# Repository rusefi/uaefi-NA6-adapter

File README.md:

# uaefi-NA6-adapter

🔴Community support ONLY 🔴

🟢 https://www.shop.rusefi.com/shop/p/uaefi-adapter-for-na6-definitely-has-issues-please-know-what-you-are-doing 🟢

To be used with https://github.com/rusefi/uaefi

powered by [rusEFI firmware](https://github.com/rusefi/rusefi)

## fun fact

See https://wiki.rusefi.com/Miata/#mazda-miata for (legacy?) open source Plug and plays

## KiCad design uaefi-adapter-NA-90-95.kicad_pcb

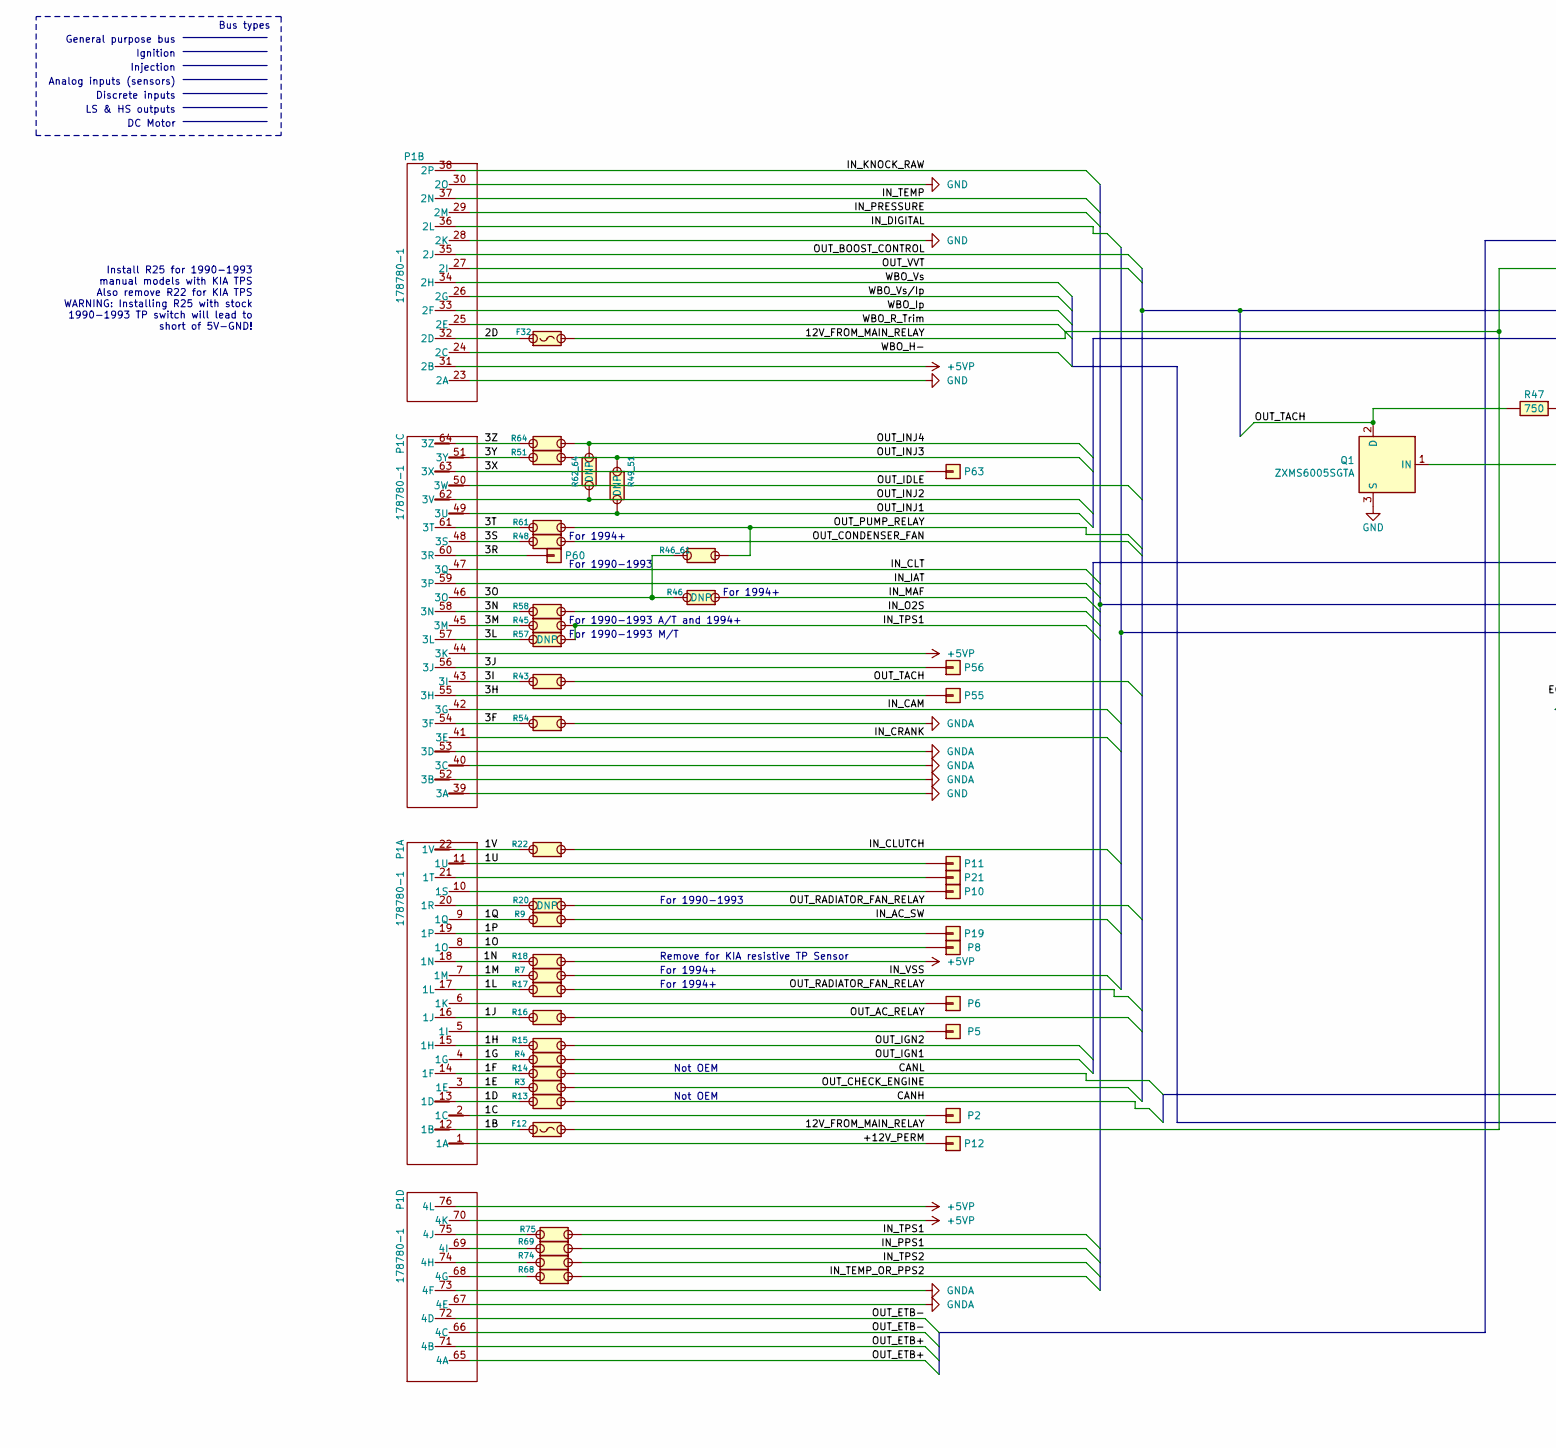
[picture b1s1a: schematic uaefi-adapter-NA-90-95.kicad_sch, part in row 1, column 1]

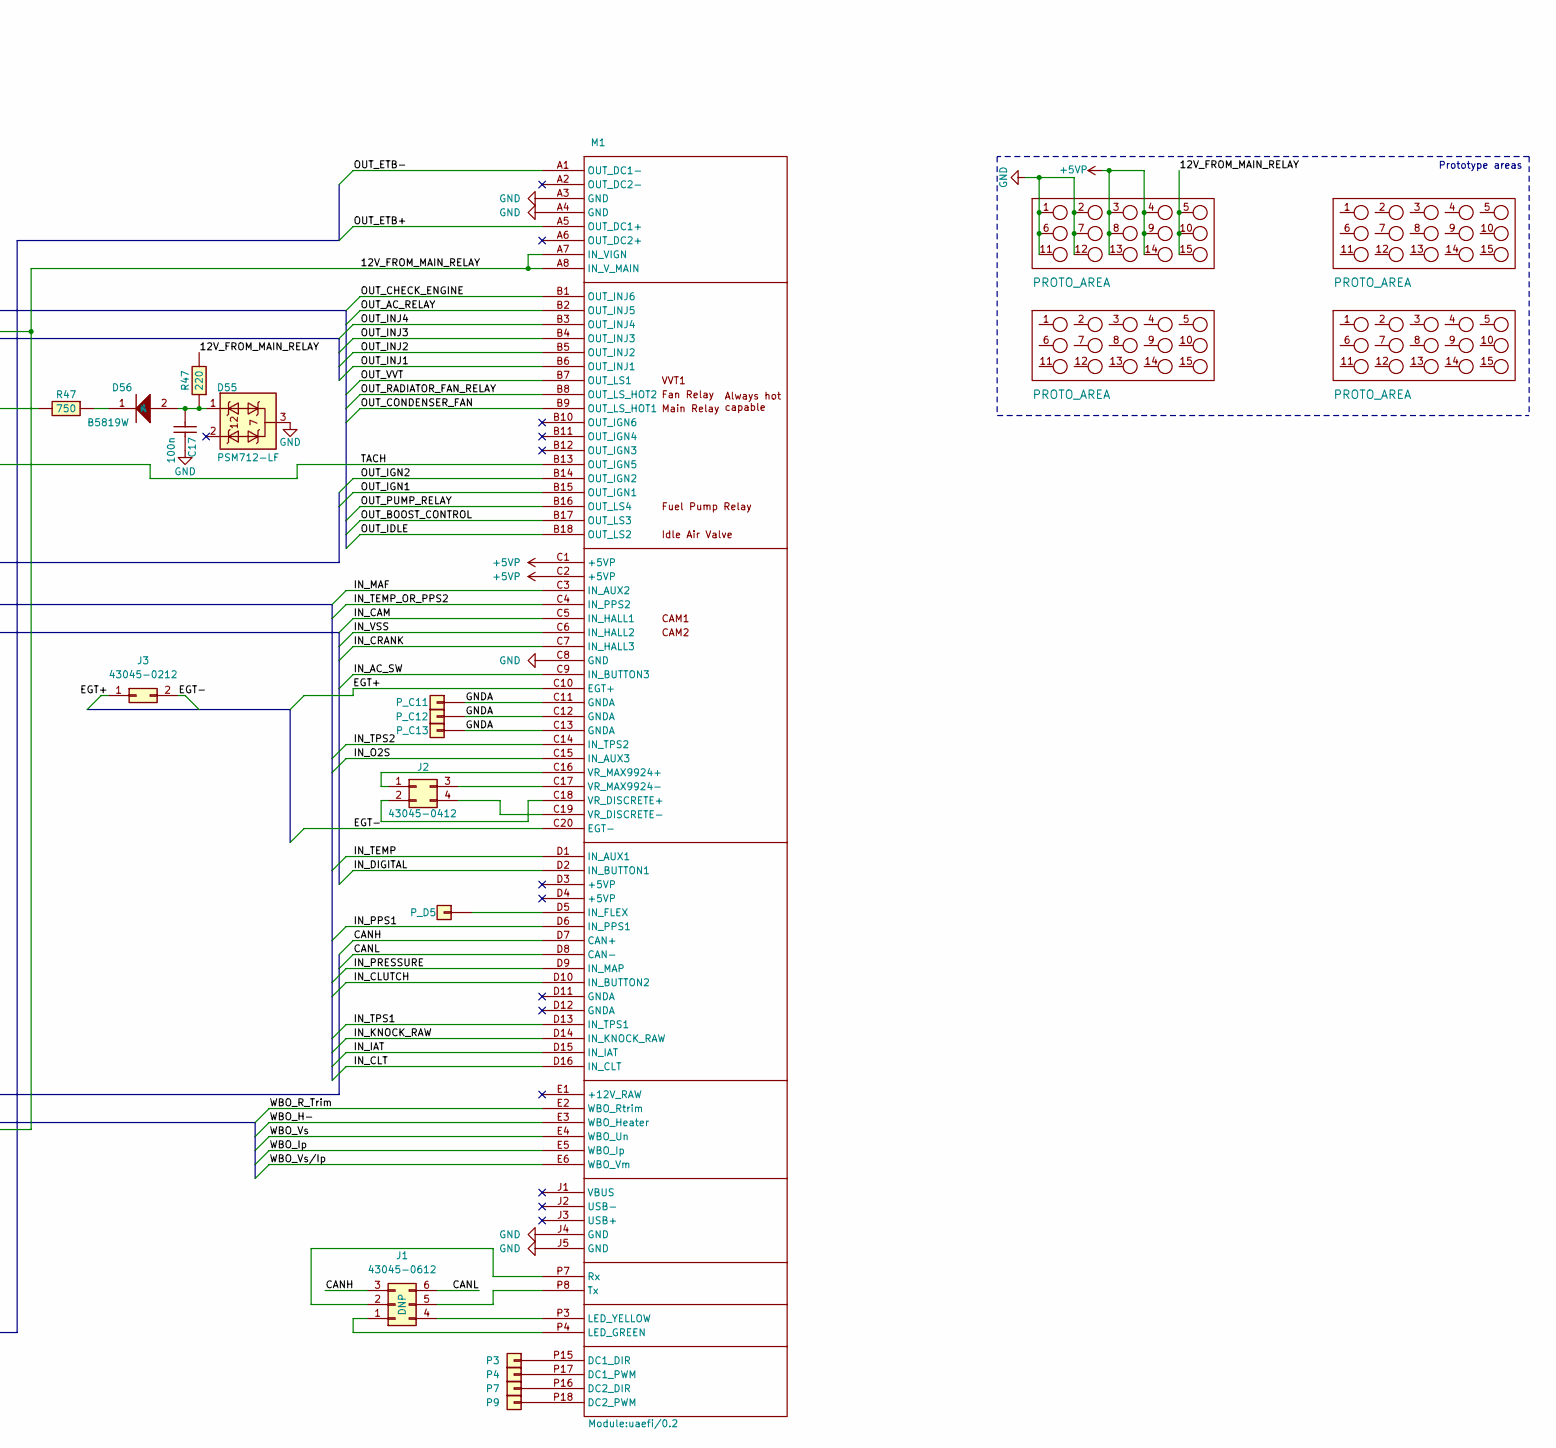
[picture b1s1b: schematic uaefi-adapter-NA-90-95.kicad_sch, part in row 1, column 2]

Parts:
C17: 100n; C0603; LCSC C14663
D55: PSM712-LF; SOT-23; LCSC C32677
D56: B5819W; SOD-123; LCSC C8598
F12, F32: Fuse-Pad-Pad; PAD-1206-PAD; LCSC C182446
G8, G9, G10, G11: PROTO_AREA
J1: 43045-0612; Molex_Micro-Fit_3.0_43045-0612_2x03_P3.00mm_Vertical
J2: 43045-0412; Molex_Micro-Fit_3.0_43045-0412_2x02_P3.00mm_Vertical
J3: 43045-0212; Molex_Micro-Fit_3.0_43045-0212_2x01_P3.00mm_Vertical; LCSC C293362
M1: Module:uaefi/0.2; uaefi
P1: 178780-1; 178780-1_OBD1
P2, P3, P4, P5, P6, P7, P8, P9, P10, P11, P12, P19, P21, P55, P56, P60, P63: Pad; PAD-TH
P_C11, P_C12, P_C13: Pad; PAD-TH
P_D5: Pad; PAD-TH
Q1: ZXMS6005SGTA; SOT-223; LCSC C174042
R3, R4, R7, R9, R13, R14, R15, R16, R17, R18, R22, R43, R45, R46_61, R48, R51, R54, R58, R61, R64, R68, R69, R74, R75: Jumper-Pad-Pad; PAD-0805-PAD; LCSC C17477
R20, R46, R49_51, R57, R62_64: Jumper-Pad-Pad; PAD-0805-PAD
R47: 220; R0805; LCSC C17557

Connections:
+5VP: G8.3, G8.4, G8.8, G8.9, G8.13, G8.14, M1.C1 (+5VP), M1.C2 (+5VP), P1.31 (2B), P1.44 (3K), P1.70 (4K), P1.76 (4L), R18.1
/1B: F12.1, P1.12 (1B)
/1C: P1.2 (1C), P2.1
/1D: P1.13 (1D), R13.2
/1E: P1.3 (1E), R3.2
/1F: P1.14 (1F), R14.2
/1G: P1.4 (1G), R4.2
/1H: P1.15 (1H), R15.2
/1J: P1.16 (1J), R16.2
/1L: P1.17 (1L), R17.2
/1M: P1.7 (1M), R7.2
/1N: P1.18 (1N), R18.2
/1O: P1.8 (1O), P8.1
/1P: P1.19 (1P), P19.1
/1Q: P1.9 (1Q), R9.2
/1U: P1.11 (1U), P11.1
/1V: P1.22 (1V), R22.2
/2D: F32.1, P1.32 (2D)
/3F: P1.54 (3F), R54.2
/3H: P1.55 (3H), P55.1
/3I: P1.43 (3I), R43.2
/3J: P1.56 (3J), P56.1
/3L: P1.57 (3L), R57.2
/3M: P1.45 (3M), R45.2
/3N: P1.58 (3N), R58.2
/3O: P1.46 (3O), R46.2, R46_61.2
/3R: P1.60 (3R), P60.1
/3S: P1.48 (3S), R48.2
/3T: P1.61 (3T), R61.2
/3X: P1.63 (3X), P63.1
/3Y: P1.51 (3Y), R51.2
/3Z: P1.64 (3Z), R64.2
/12V_FROM_MAIN_RELAY: F12.2, F32.2, G8.5, G8.10, G8.15, M1.A7 (IN_VIGN), M1.A8 (IN_V_MAIN); also elsewhere on the board
/+12V_PERM: P1.1 (1A), P12.1
/CANH: J1.3, M1.D7 (CAN+), R13.1
/CANL: J1.6, M1.D8 (CAN-), R14.1
/EGT+: J3.1, M1.C10 (EGT+)
/EGT-: J3.2, M1.C20 (EGT-)
/IN_AC_SW: M1.C9 (IN_BUTTON3), R9.1
/IN_CAM: M1.C5 (IN_HALL1), P1.42 (3G)
/IN_CLT: M1.D16 (IN_CLT), P1.47 (3Q)
/IN_CLUTCH: M1.D10 (IN_BUTTON2), R22.1
/IN_CRANK: M1.C7 (IN_HALL3), P1.41 (3E)
/IN_DIGITAL: M1.D2 (IN_BUTTON1), P1.36 (2L)
/IN_IAT: M1.D15 (IN_IAT), P1.59 (3P)
/IN_KNOCK_RAW: M1.D14 (IN_KNOCK_RAW), P1.38 (2P)
/IN_MAF: M1.C3 (IN_AUX2), R46.1
/IN_O2S: M1.C15 (IN_AUX3), R58.1
/IN_PPS1: M1.D6 (IN_PPS1), R69.1
/IN_PRESSURE: M1.D9 (IN_MAP), P1.29 (2M)
/IN_TEMP: M1.D1 (IN_AUX1), P1.37 (2N)
/IN_TEMP_OR_PPS2: M1.C4 (IN_PPS2), R68.1
/IN_TPS1: M1.D13 (IN_TPS1), R45.1, R57.1, R75.1
/IN_TPS2: M1.C14 (IN_TPS2), R74.1
/IN_VSS: M1.C6 (IN_HALL2), R7.1
/OUT_AC_RELAY: M1.B2 (OUT_INJ5), R16.1
/OUT_BOOST_CONTROL: M1.B17 (OUT_LS3), P1.35 (2J)
/OUT_CHECK_ENGINE: M1.B1 (OUT_INJ6), R3.1
/OUT_CONDENSER_FAN: M1.B9 (OUT_LS_HOT1), R48.1
/OUT_ETB+: M1.A5 (OUT_DC1+), P1.65 (4A), P1.71 (4B)
/OUT_ETB-: M1.A1 (OUT_DC1-), P1.66 (4C), P1.72 (4D)
/OUT_IDLE: M1.B18 (OUT_LS2), P1.50 (3W)
/OUT_IGN1: M1.B15 (OUT_IGN1), R4.1
/OUT_IGN2: M1.B14 (OUT_IGN2), R15.1
/OUT_INJ1: M1.B6 (OUT_INJ1), P1.49 (3U), R49_51.2
/OUT_INJ2: M1.B5 (OUT_INJ2), P1.62 (3V), R62_64.2
/OUT_INJ3: M1.B4 (OUT_INJ3), R49_51.1, R51.1
/OUT_INJ4: M1.B3 (OUT_INJ4), R62_64.1, R64.1
/OUT_PUMP_RELAY: M1.B16 (OUT_LS4), R46_61.1, R61.1
/OUT_RADIATOR_FAN_RELAY: M1.B8 (OUT_LS_HOT2), R17.1, R20.1
/OUT_TACH: Q1.2 (D), R43.1; also elsewhere on the board
/OUT_VVT: M1.B7 (OUT_LS1), P1.27 (2I)
/TACH: M1.B13 (OUT_IGN5), Q1.1 (IN)
/WBO_H-: M1.E3 (WBO_Heater), P1.24 (2C)
/WBO_Ip: M1.E5 (WBO_Ip), P1.33 (2F)
/WBO_R_Trim: M1.E2 (WBO_Rtrim), P1.25 (2E)
/WBO_Vs: M1.E4 (WBO_Un), P1.34 (2H)
/WBO_Vs/Ip: M1.E6 (WBO_Vm), P1.26 (2G)
GND: G8.1, G8.2, G8.6, G8.7, G8.11, G8.12, M1.A3 (GND), M1.A4 (GND), M1.C8 (GND), M1.J4 (GND), M1.J5 (GND), P1.23 (2A), P1.28 (2K), P1.30 (2O), P1.39 (3A), Q1.3 (S); also elsewhere on the board
GNDA: M1.C11 (GNDA), M1.C12 (GNDA), M1.C13 (GNDA), P1.40 (3C), P1.52 (3B), P1.53 (3D), P1.67 (4E), P1.73 (4F), P_C11.1, P_C12.1, P_C13.1, R54.1
unnamed: J1.1, M1.P4 (LED_GREEN)
unnamed: J1.2, M1.P7 (Rx)
unnamed: J1.4, M1.P3 (LED_YELLOW)
unnamed: J1.5, M1.P8 (Tx)
unnamed: J2.1, M1.C16 (VR_MAX9924+)
unnamed: J2.2, M1.C18 (VR_DISCRETE+)
unnamed: J2.3, M1.C17 (VR_MAX9924-)
unnamed: J2.4, M1.C19 (VR_DISCRETE-)
unnamed: M1.P15 (DC1_DIR), P3.1
unnamed: M1.P17 (DC1_PWM), P4.1
unnamed: M1.P16 (DC2_DIR), P7.1
unnamed: M1.P18 (DC2_PWM), P9.1
unnamed: M1.D5 (IN_FLEX), P_D5.1
unnamed: P1.5 (1I), P5.1
unnamed: P1.6 (1K), P6.1
unnamed: P1.20 (1R), R20.2
unnamed: P1.21 (1T), P21.1
unnamed: P1.68 (4G), R68.2
unnamed: P1.74 (4H), R74.2
unnamed: P1.69 (4I), R69.2
unnamed: P1.75 (4J), R75.2
unnamed: P1.10 (1S), P10.1

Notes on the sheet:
For 1994+
Injection
For 1990-1993
Discrete inputs
Not OEM
General purpose bus
For 1990-1993
Bus types
For 1994+
LS & HS outputs
Install R25 for 1990-1993 manual models with KIA TPS Also remove R22 for KIA TPS WARNING: Installing R25 with stock 1990-1993 TP switch will lead to short of 5V-GND!
For 1990-1993 M/T
For 1990-1993 A/T and 1994+
DC Motor
Prototype areas
Ignition
Remove for KIA resistive TP Sensor
Analog inputs (sensors)

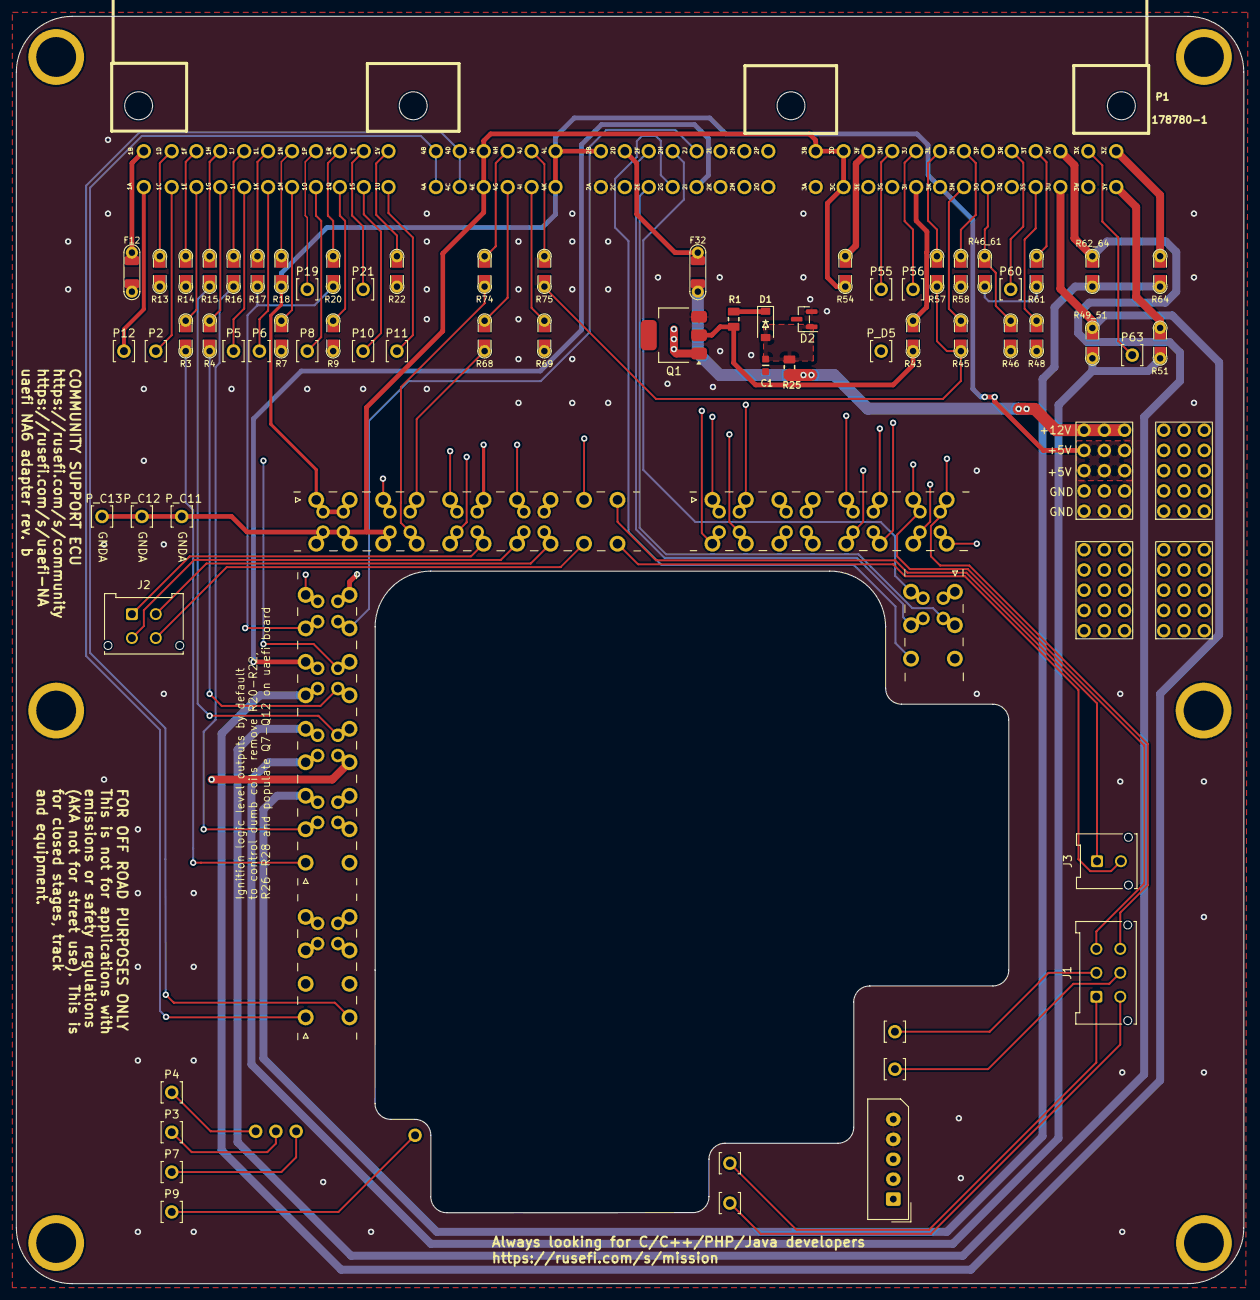
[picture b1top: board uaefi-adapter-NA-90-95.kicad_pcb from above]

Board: 4 copper layers, 154.0 x 159.0 mm, 73 parts (0 on the bottom side), 104 nets.

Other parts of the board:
C1: 100n; C0603
D1: B5819W; SOD-123
D2: PSM712-LF; SOT-23
J11, J13, J14, J15, J16, J17: Conn_01x01; MountingHole_4.5mm_Pad
R1: 750; R0805
R25: 220; R0805

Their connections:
/12V_FROM_MAIN_RELAY: R25.2; also elsewhere on the board
/OUT_TACH: R1.2; also elsewhere on the board
GND: C1.1, D2.3; also elsewhere on the board
unnamed: C1.2, D1.2 (A), D2.1, R25.1
unnamed: D1.1 (K), R1.1

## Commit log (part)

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2024-01-12 .gitignore
2024-01-12 how about?
2024-01-12 empty
2024-01-12 progress
2024-01-17 project local
2024-02-25 hellen
2024-02-25 auto-refresh
2024-02-26 GHA says update kicad6-libraries
2024-02-28 GHA says update hellen-one
2024-03-03 Upd SCH
2024-03-03 Update kicad6-libraries
2024-03-05 Update fp-lib-table
2024-03-10 in progress
2024-03-12 [skip actions] Auto-generated board v2.1
2024-03-13 docs
2025-09-02 rev b
2025-09-02 #18 #19
2025-09-03 4 layers
